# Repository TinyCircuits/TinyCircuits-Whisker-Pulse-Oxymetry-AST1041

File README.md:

# TinyCircuits Wireling Pulse Oximetry
# AST1041 Rev1

The design files are located under design_files/ for the TinyCircuits AST1041 Rev 1 PCB. This is a Wireling board which features the MAX30101, an integrated pulse oximetry and heart-rate monitor module. 

Format is in Cadsoft Eagle format - Eagle version 6.2 was used for the original design.

For more infomation on this, check out the product page at TinyCircuits.com

# License:

Design by TinyCircuits.
All design files are released under the Creative Commons Attribution Share-Alike 3.0 License, see the following link for details: http://creativecommons.org/licenses/by-sa/3.0

All text above must be included in any redistribution or derived design

This project uses designs and concepts developed as part of the Arduino project and the LilyPad project.  The TinyCircuits design files themselves (schematics, PCB and libraries) are not directly derived from these works' design files and have been created new, however the concepts and basic architecture behind the TinyDuino and TinyLily products are derived and we thank the hard work of the organizations below for their contributions to open-source hardware:
  
Original Arduino Uno Design by Team Arduino

LilyPad Arduino Design by Leah Buechley and Sparkfun Electronics

Please support the open-source hardware community

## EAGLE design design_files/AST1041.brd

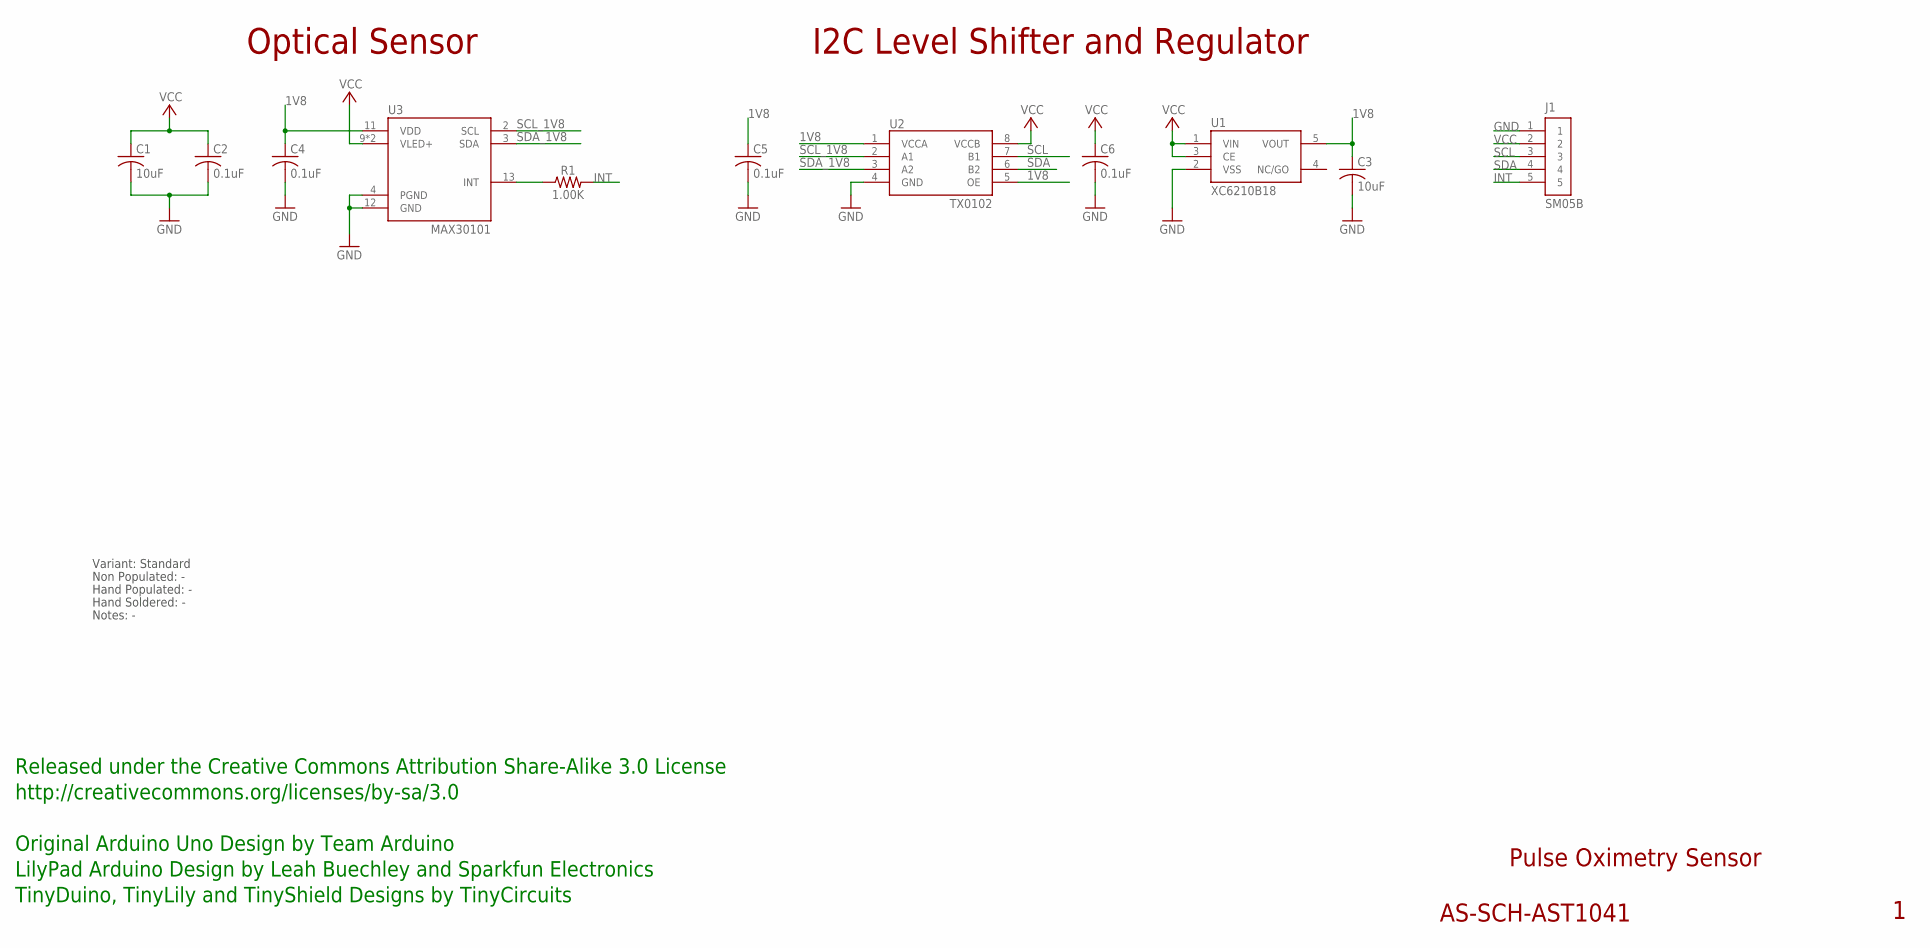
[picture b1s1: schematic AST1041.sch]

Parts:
C1, C3: 10uF; C0603; PARTNO AS-ITM-00002
C2: 0.1uF; C0402
C4, C5, C6: 0.1uF; C0402; PARTNO AS-ITM-00008
J1: SM05B; JST_SH_5X1
R1: 1.00K; 0402
U1: XC6210B18; SOT-25@1
U2: TX0102; DQE(R-PX2SON-N8)
U3: MAX30101; MAX30100

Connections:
1V8: C3.1, C4.1, C5.1, U1.5 (VOUT), U2.1 (VCCA), U2.5 (OE), U3.11 (VDD)
GND: C1.2, C2.2, C3.2, C4.2, C5.2, C6.2, J1.1, U1.2 (VSS), U2.4 (GND), U3.4 (PGND), U3.12 (GND)
INT: J1.5, R1.2
unnamed: R1.1, U3.13 (INT)
SCL: J1.3, U2.7 (B1)
SCL_1V8: U2.2 (A1), U3.2 (SCL)
SDA: J1.4, U2.6 (B2)
SDA_1V8: U2.3 (A2), U3.3 (SDA)
VCC: C1.1, C2.1, C6.1, J1.2, U1.1 (VIN), U1.3 (CE), U2.8 (VCCB), U3.9 (VLED+), U3.10 (VLED+)

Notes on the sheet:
Pulse Oximetry Sensor
AS-SCH-AST1041
Optical Sensor
Released under the Creative Commons Attribution Share-Alike 3.0 License
http://creativecommons.org/licenses/by-sa/3.0
Original Arduino Uno Design by Team Arduino
TinyDuino, TinyLily and TinyShield Designs by TinyCircuits
LilyPad Arduino Design by Leah Buechley and Sparkfun Electronics
I2C Level Shifter and Regulator
Non Populated: -
Hand Populated: -
Hand Soldered: -
Notes: -
Variant: Standard

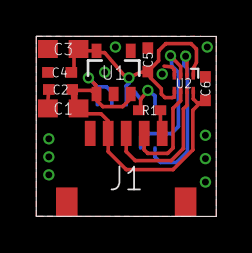
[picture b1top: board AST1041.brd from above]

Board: 2 copper layers, 10.0 x 10.0 mm, 12 parts (1 on the bottom side), 9 nets.

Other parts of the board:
U$1: DOCFIELD-TINYCIRCUITS-PCB

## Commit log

2019-08-05 added datasheet
2019-12-17 updated documentation
2019-12-30 added images
2019-12-31 removed fake switch
2020-02-04 mass image update
2020-05-19 fix images
2020-05-20 output images
2020-08-14 Add CAD data
